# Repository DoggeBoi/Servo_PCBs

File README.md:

# Servo_PCBs
Collection of proof of consept and "production" PCBs 

Test PCB

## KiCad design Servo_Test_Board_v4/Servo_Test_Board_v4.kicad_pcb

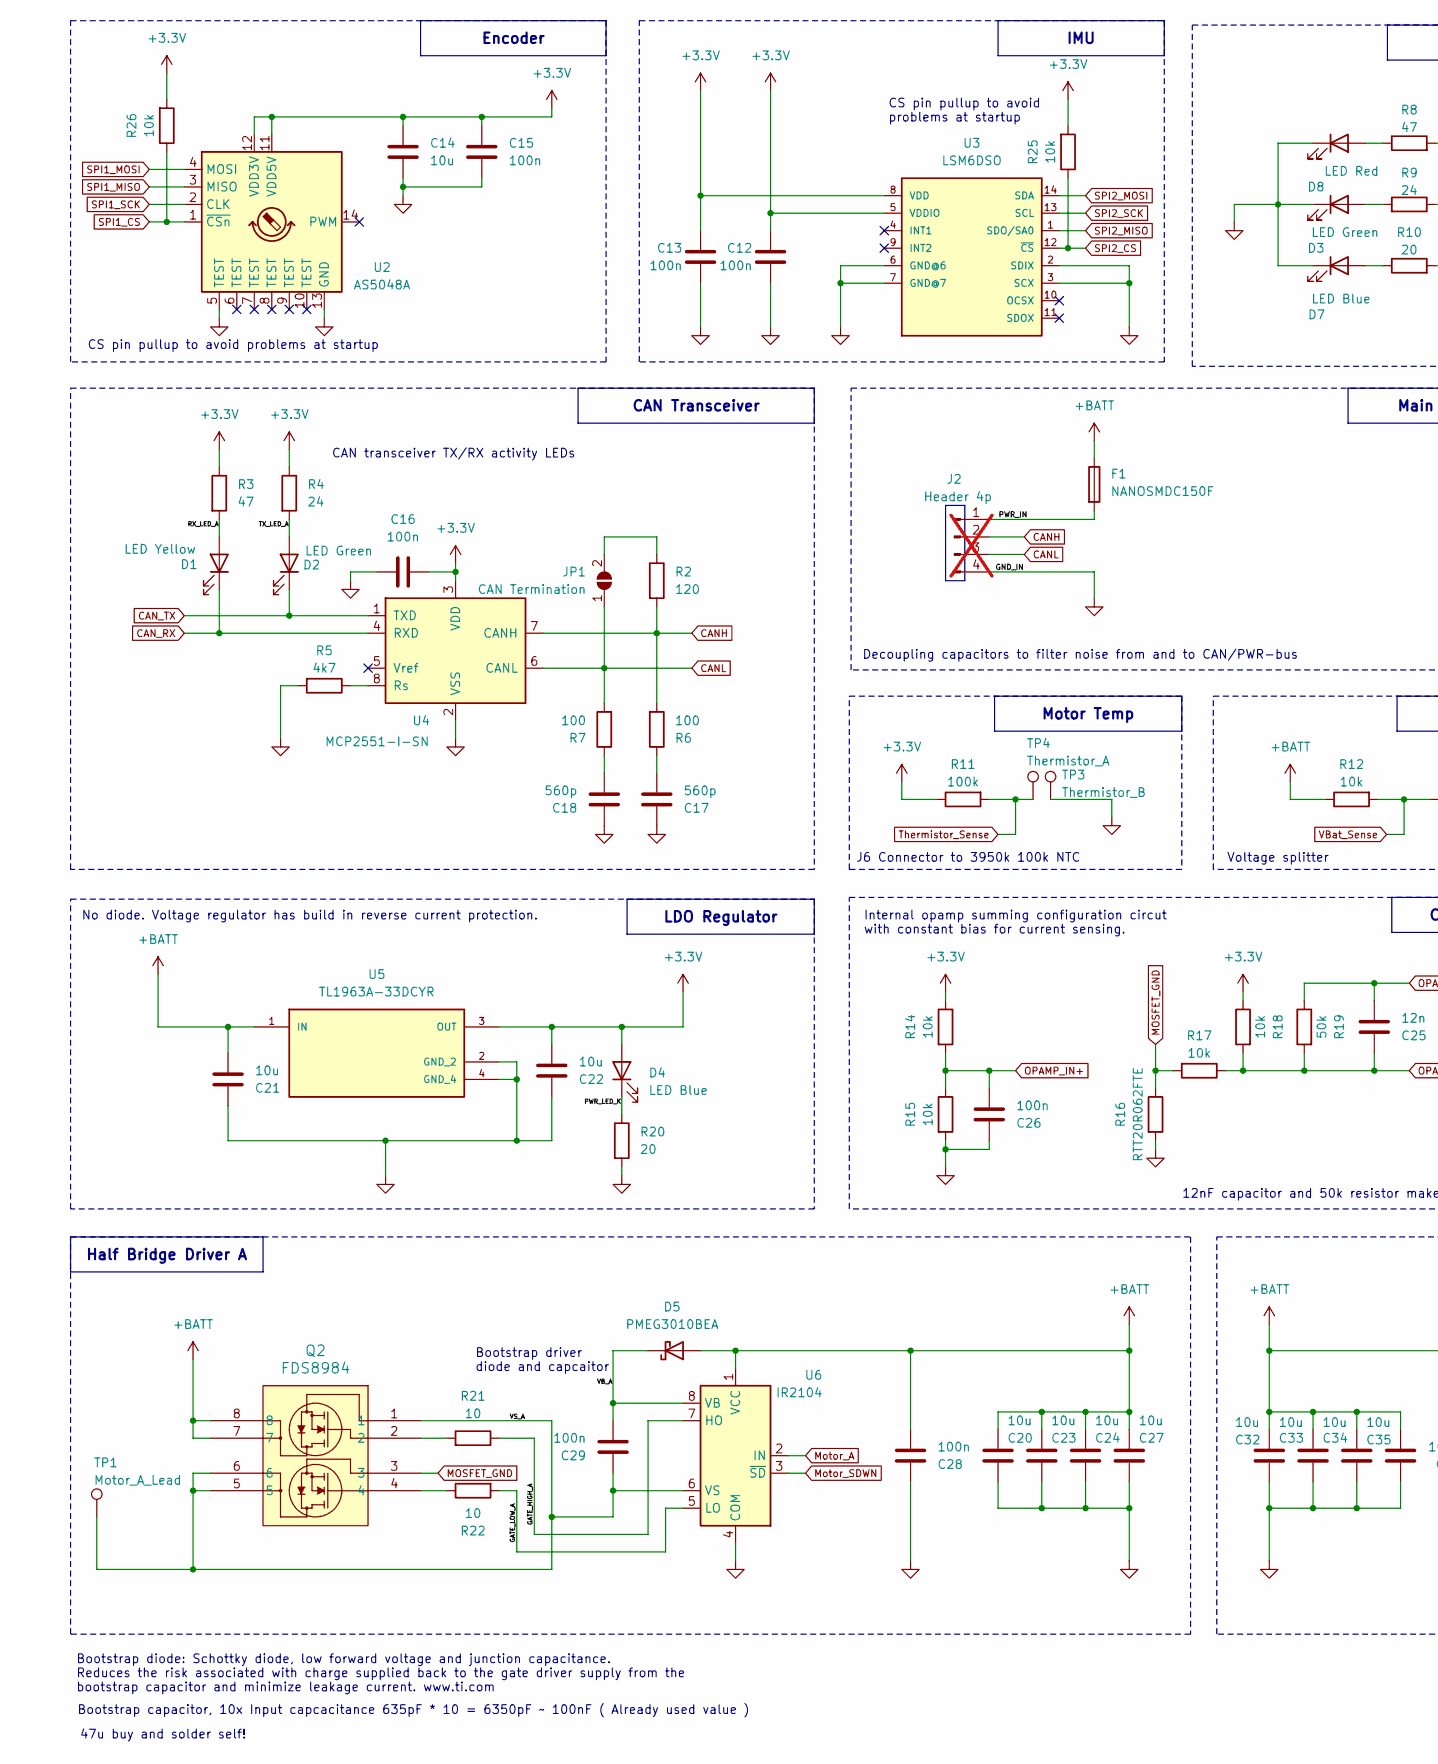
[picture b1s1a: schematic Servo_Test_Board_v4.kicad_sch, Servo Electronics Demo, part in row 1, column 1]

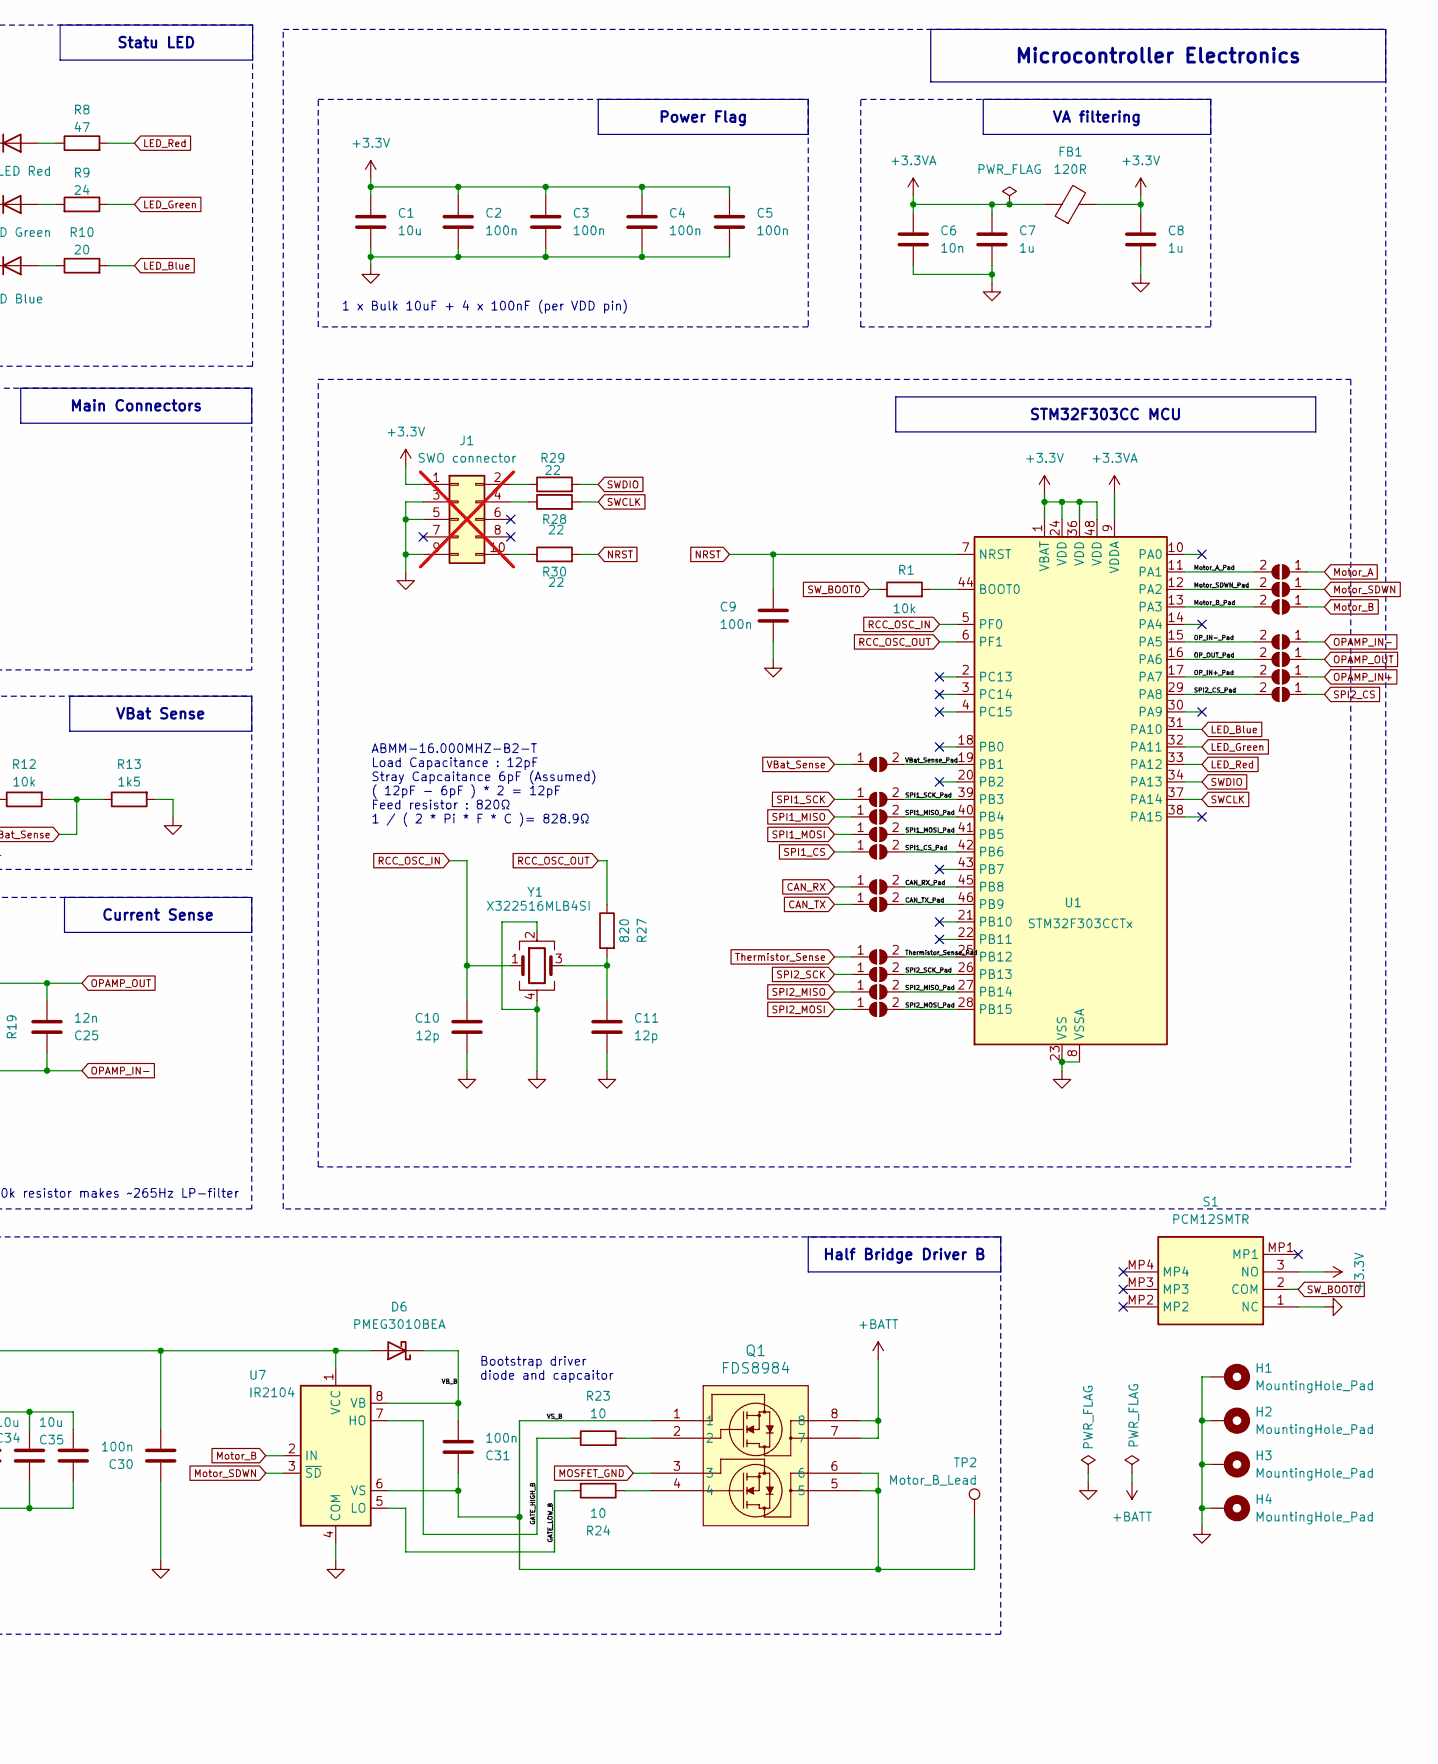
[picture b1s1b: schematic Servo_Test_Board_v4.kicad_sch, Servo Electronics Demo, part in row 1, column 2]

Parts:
C1, C14, C20, C21, C22, C23, C24, C27, C32, C33, C34, C35: 10u; C_0805_2012Metric
C2, C3, C4, C5, C9, C12, C13, C15, C16, C26, C28, C29, C30, C31: 100n; C_0402_1005Metric
C6: 10n; C_0402_1005Metric
C7, C8: 1u; C_0402_1005Metric
C10, C11: 12p; C_0402_1005Metric
C17, C18: 560p; C_0402_1005Metric
C25: 12n; C_0402_1005Metric
D1: LED Yellow; LED_0603_1608Metric
D2, D3: LED Green; LED_0603_1608Metric
D4, D7: LED Blue; LED_0603_1608Metric
D5, D6: PMEG3010BEA; D_SOD-323
D8: LED Red; LED_0603_1608Metric
F1: NANOSMDC150F; Fuse_1206_3216Metric
FB1: 120R; L_0603_1608Metric
H1, H2, H3, H4: MountingHole_Pad; MountingHole_3.2mm_M3_Pad_Via
J1: SWO connector; PinSocket_2x05_P2.54mm_Vertical; not fitted
J2: Header 4p; PinSocket_1x04_P2.54mm_Vertical; not fitted
JP1: CAN Termination; SolderJumper-2_P1.3mm_Open_RoundedPad1.0x1.5mm
JP2, JP3, JP4, JP5, JP6, JP7, JP8, JP9, JP10, JP11, JP12, JP14, JP15, JP16, JP17, JP18, JP19, JP20: SolderJumper_2_Open; SolderJumper-2_P1.3mm_Open_RoundedPad1.0x1.5mm
Q1, Q2: FDS8984; SOIC-8_3.9x4.9mm_P1.27mm
R1, R12, R14, R15, R17, R18, R25, R26: 10k; R_0402_1005Metric
R2: 120; R_0805_2012Metric
R3, R8: 47; R_0402_1005Metric
R4, R9: 24; R_0402_1005Metric
R5: 4k7; R_0402_1005Metric
R6, R7: 100; R_0402_1005Metric
R10, R20: 20; R_0402_1005Metric
R11: 100k; R_0402_1005Metric
R13: 1k5; R_0402_1005Metric
R16: RTT20R062FTE; R_2010_5025Metric_Pad1.40x2.65mm_HandSolder
R19: 50k; R_0402_1005Metric
R21, R22, R23, R24: 10; R_0402_1005Metric
R27: 820; R_0402_1005Metric
R28, R29, R30: 22; R_0402_1005Metric
S1: PCM12SMTR; Mouser Part Number 611-PCM12SMTR
TP1: Motor_A_Lead; TestPoint_Pad_2.5x2.5mm
TP2: Motor_B_Lead; TestPoint_Pad_2.5x2.5mm
TP3: Thermistor_B; TestPoint_Pad_2.0x2.0mm
TP4: Thermistor_A; TestPoint_Pad_2.0x2.0mm
U1: STM32F303CCTx; LQFP-48_7x7mm_P0.5mm
U2: AS5048A; TSSOP-14_4.4x5mm_P0.65mm
U3: LSM6DSO; LGA14L
U4: MCP2551-I-SN; SOIC-8_3.9x4.9mm_P1.27mm
U5: TL1963A-33DCYR; VREG_TL1963A-33DCYR; PARTREV G
U6, U7: IR2104; SOIC127P600X175-8N
Y1: X322516MLB4SI; Crystal_SMD_3225-4Pin_3.2x2.5mm

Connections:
+3.3V: C1.1, C2.1, C3.1, C4.1, C5.1, C8.1, C12.1, C13.1, C14.1, C15.1, C16.2, C22.1, D4.2 (A), FB1.2, J1.1, R3.1, R4.1, R11.1, R14.1, R18.1, R25.2, R26.2, S1.3 (NO), U1.1 (VBAT), U1.24 (VDD), U1.36 (VDD), U1.48 (VDD), U2.11 (VDD5V), U2.12 (VDD3V), U3.5 (VDDIO), U3.8 (VDD), U4.3 (VDD), U5.3 (OUT)
+3.3VA: C6.1, C7.1, FB1.1, U1.9 (VDDA)
+BATT: C20.1, C21.1, C23.1, C24.1, C27.1, C28.1, C30.1, C32.1, C33.1, C34.1, C35.1, D5.2 (A), D6.2 (A), F1.1, Q1.7, Q1.8, Q2.7, Q2.8, R12.1, U5.1 (IN), U6.1 (VCC), U7.1 (VCC)
/CAN_RX_Pad: JP7.2 (B), U1.45 (PB8)
/CAN_TX_Pad: JP8.2 (B), U1.46 (PB9)
/GATE_HIGH_A: R21.1, U6.7 (HO)
/GATE_HIGH_B: R23.1, U7.7 (HO)
/GATE_LOW_A: R22.2, U6.5 (LO)
/GATE_LOW_B: R24.2, U7.5 (LO)
/Motor_A_Pad: JP14.2 (B), U1.11 (PA1)
/Motor_B_Pad: JP16.2 (B), U1.13 (PA3)
/Motor_SDWN_Pad: JP15.2 (B), U1.12 (PA2)
/OP_IN+_Pad: JP19.2 (B), U1.17 (PA7)
/OP_IN-_Pad: JP17.2 (B), U1.15 (PA5)
/OP_OUT_Pad: JP18.2 (B), U1.16 (PA6)
/PWR_IN: F1.2, J2.1
/PWR_LED_K: D4.1 (K), R20.1
/RX_LED_A: D1.2 (A), R3.2
/SPI1_CS_Pad: JP6.2 (B), U1.42 (PB6)
/SPI1_MISO_Pad: JP4.2 (B), U1.40 (PB4)
/SPI1_MOSI_Pad: JP5.2 (B), U1.41 (PB5)
/SPI1_SCK_Pad: JP3.2 (B), U1.39 (PB3)
/SPI2_CS_Pad: JP20.2 (B), U1.29 (PA8)
/SPI2_MISO_Pad: JP11.2 (B), U1.27 (PB14)
/SPI2_MOSI_Pad: JP12.2 (B), U1.28 (PB15)
/SPI2_SCK_Pad: JP10.2 (B), U1.26 (PB13)
/TX_LED_A: D2.2 (A), R4.2
/Thermistor_Sense_Pad: JP9.2 (B), U1.25 (PB12)
/VB_A: C29.1, D5.1 (K), U6.8 (VB)
/VB_B: C31.1, D6.1 (K), U7.8 (VB)
/VBat_Sense_Pad: JP2.2 (B), U1.19 (PB1)
/VS_A: C29.2, Q2.1, Q2.5, Q2.6, TP1.1, U6.6 (VS)
/VS_B: C31.2, Q1.1, Q1.5, Q1.6, TP2.1, U7.6 (VS)
CANH: J2.2, R2.2, R6.2, U4.7 (CANH)
CANL: J2.3, JP1.1 (A), R7.2, U4.6 (CANL)
CAN_RX: D1.1 (K), JP7.1 (A), U4.4 (RXD)
CAN_TX: D2.1 (K), JP8.1 (A), U4.1 (TXD)
GND: C1.2, C2.2, C3.2, C4.2, C5.2, C6.2, C7.2, C8.2, C9.2, C10.2, C11.2, C12.2, C13.2, C14.2, C15.2, C16.1, C17.2, C18.2, C20.2, C21.2, C22.2, C23.2, C24.2, C26.2, C27.2, C28.2, C30.2, C32.2, C33.2, C34.2, C35.2, D3.1 (K), D7.1 (K), D8.1 (K), H1.1, H2.1, H3.1, H4.1, J1.3, J1.5, J1.9, J2.4, R5.2, R13.2, R15.2, R16.2, R20.2, S1.1 (NC), TP3.1, U1.8 (VSSA), U1.23 (VSS), U1.35 (VSS), U1.47 (VSS), U2.5 (TEST), U2.13 (GND), U3.2 (SDIX), U3.3 (SCX), U3.6 (GND@6), U3.7 (GND@7), U4.2 (VSS), U5.2 (GND_2), U5.4 (GND_4), U6.4 (COM), U7.4 (COM), Y1.2, Y1.4
LED_Blue: R10.2, U1.31 (PA10)
LED_Green: R9.1, U1.32 (PA11)
LED_Red: R8.2, U1.33 (PA12)
MOSFET_GND: Q1.3, Q2.3, R16.1, R17.2
Motor_A: JP14.1 (A), U6.2 (IN)
Motor_B: JP16.1 (A), U7.2 (IN)
Motor_SDWN: JP15.1 (A), U6.3 (~SD), U7.3 (~SD)
NRST: C9.1, R30.2, U1.7 (NRST)
unnamed: C11.1, R27.2, Y1.3
unnamed: C17.1, R6.1
unnamed: C18.1, R7.1
unnamed: D3.2 (A), R9.2
unnamed: D7.2 (A), R10.1
unnamed: D8.2 (A), R8.1
unnamed: J1.2, R29.1
unnamed: J1.4, R28.1
unnamed: J1.10, R30.1
unnamed: JP1.2 (B), R2.1
unnamed: Q1.2, R23.2
unnamed: Q1.4, R24.1
unnamed: Q2.2, R21.2
unnamed: Q2.4, R22.1
unnamed: R1.2, U1.44 (BOOT0)
unnamed: R5.1, U4.8 (Rs)
OPAMP_IN+: C26.1, JP19.1 (A), R14.2, R15.1
OPAMP_IN-: C25.2, JP17.1 (A), R17.1, R18.2, R19.2
OPAMP_OUT: C25.1, JP18.1 (A), R19.1
RCC_OSC_IN: C10.1, U1.5 (PF0), Y1.1
RCC_OSC_OUT: R27.1, U1.6 (PF1)
SPI1_CS: JP6.1 (A), R26.1, U2.1 (~CSn)
SPI1_MISO: JP4.1 (A), U2.3 (MISO)
SPI1_MOSI: JP5.1 (A), U2.4 (MOSI)
SPI1_SCK: JP3.1 (A), U2.2 (CLK)
SPI2_CS: JP20.1 (A), R25.1, U3.12 (~CS)
SPI2_MISO: JP11.1 (A), U3.1 (SDO/SA0)
SPI2_MOSI: JP12.1 (A), U3.14 (SDA)
SPI2_SCK: JP10.1 (A), U3.13 (SCL)
SWCLK: R28.2, U1.37 (PA14)
SWDIO: R29.2, U1.34 (PA13)
SW_BOOT0: R1.1, S1.2 (COM)
Thermistor_Sense: JP9.1 (A), R11.2, TP4.1
VBat_Sense: JP2.1 (A), R12.2, R13.1

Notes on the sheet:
Main Connectors
Power Flag
Half Bridge Driver B
STM32F303CC MCU
Current Sense
Statu LED
IMU
LDO Regulator
Microcontroller Electronics
VBat Sense
Motor Temp
Encoder
CAN Transceiver
VA filtering
Half Bridge Driver A
Bootstrap capacitor, 10x Input capcacitance 635pF * 10 = 6350pF ~ 100nF ( Already used value )
Bootstrap diode: Schottky diode, low forward voltage and junction capacitance. Reduces the risk associated with charge supplied back to the gate driver supply from the bootstrap capacitor and minimize leakage current. www.ti.com
No diode. Voltage regulator has build in reverse current protection.
Decoupling capacitors to filter noise from and to CAN/PWR-bus
Bootstrap driver diode and capcaitor
ABMM-16.000MHZ-B2-T Load Capacitance : 12pF Stray Capcaitance 6pF (Assumed) ( 12pF - 6pF ) * 2 = 12pF Feed resistor : 820Ω 1 / ( 2 * Pi * F * C )= 828.9Ω
12nF capacitor and 50k resistor makes ~265Hz LP-filter
CS pin pullup to avoid problems at startup
CS pin pullup to avoid problems at startup
Internal opamp summing configuration circut with constant bias for current sensing.
Voltage splitter
CAN transceiver TX/RX activity LEDs
47u buy and solder self!
1 x Bulk 10uF + 4 x 100nF (per VDD pin)
J6 Connector to 3950k 100k NTC

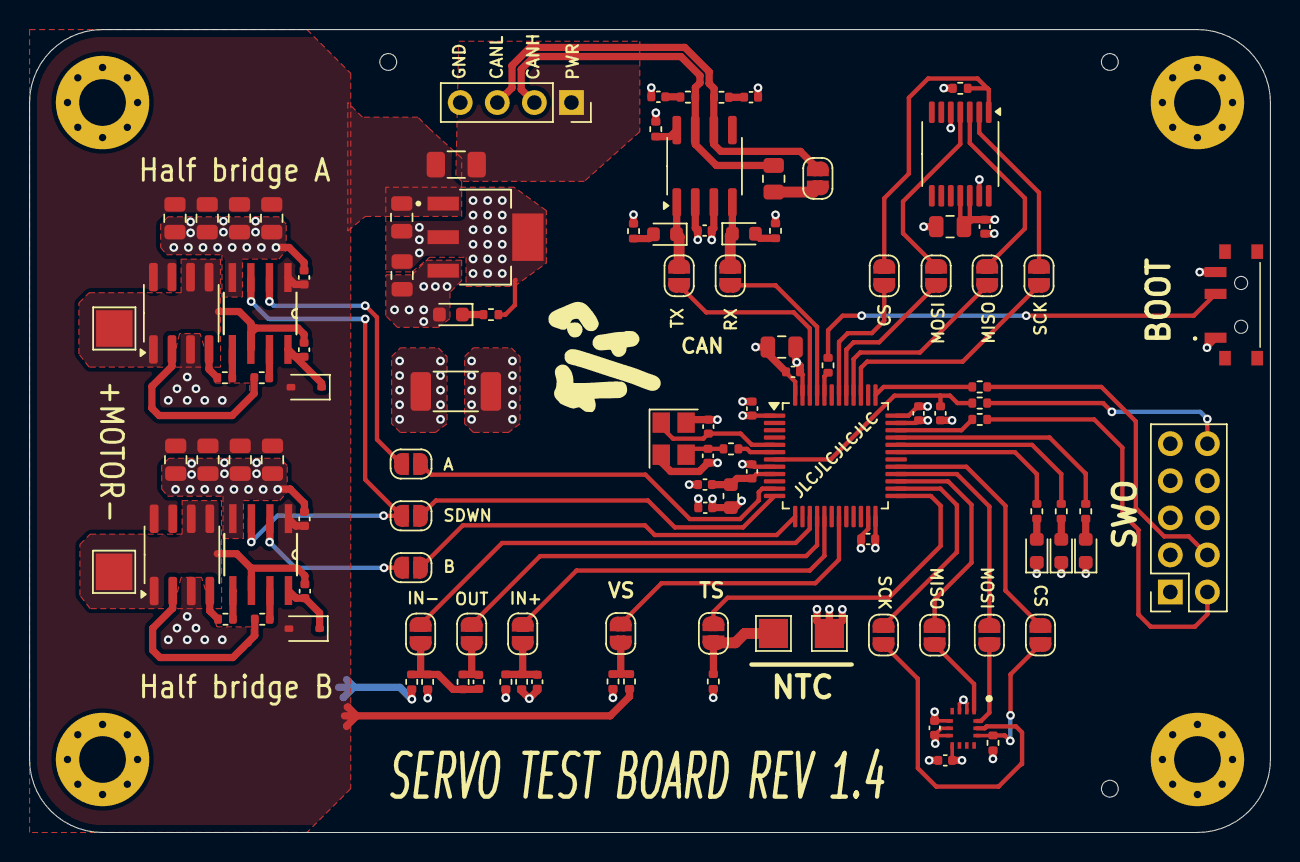
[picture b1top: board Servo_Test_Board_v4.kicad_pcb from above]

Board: 4 copper layers, 85.0 x 55.0 mm, 114 parts (0 on the bottom side), 80 nets.

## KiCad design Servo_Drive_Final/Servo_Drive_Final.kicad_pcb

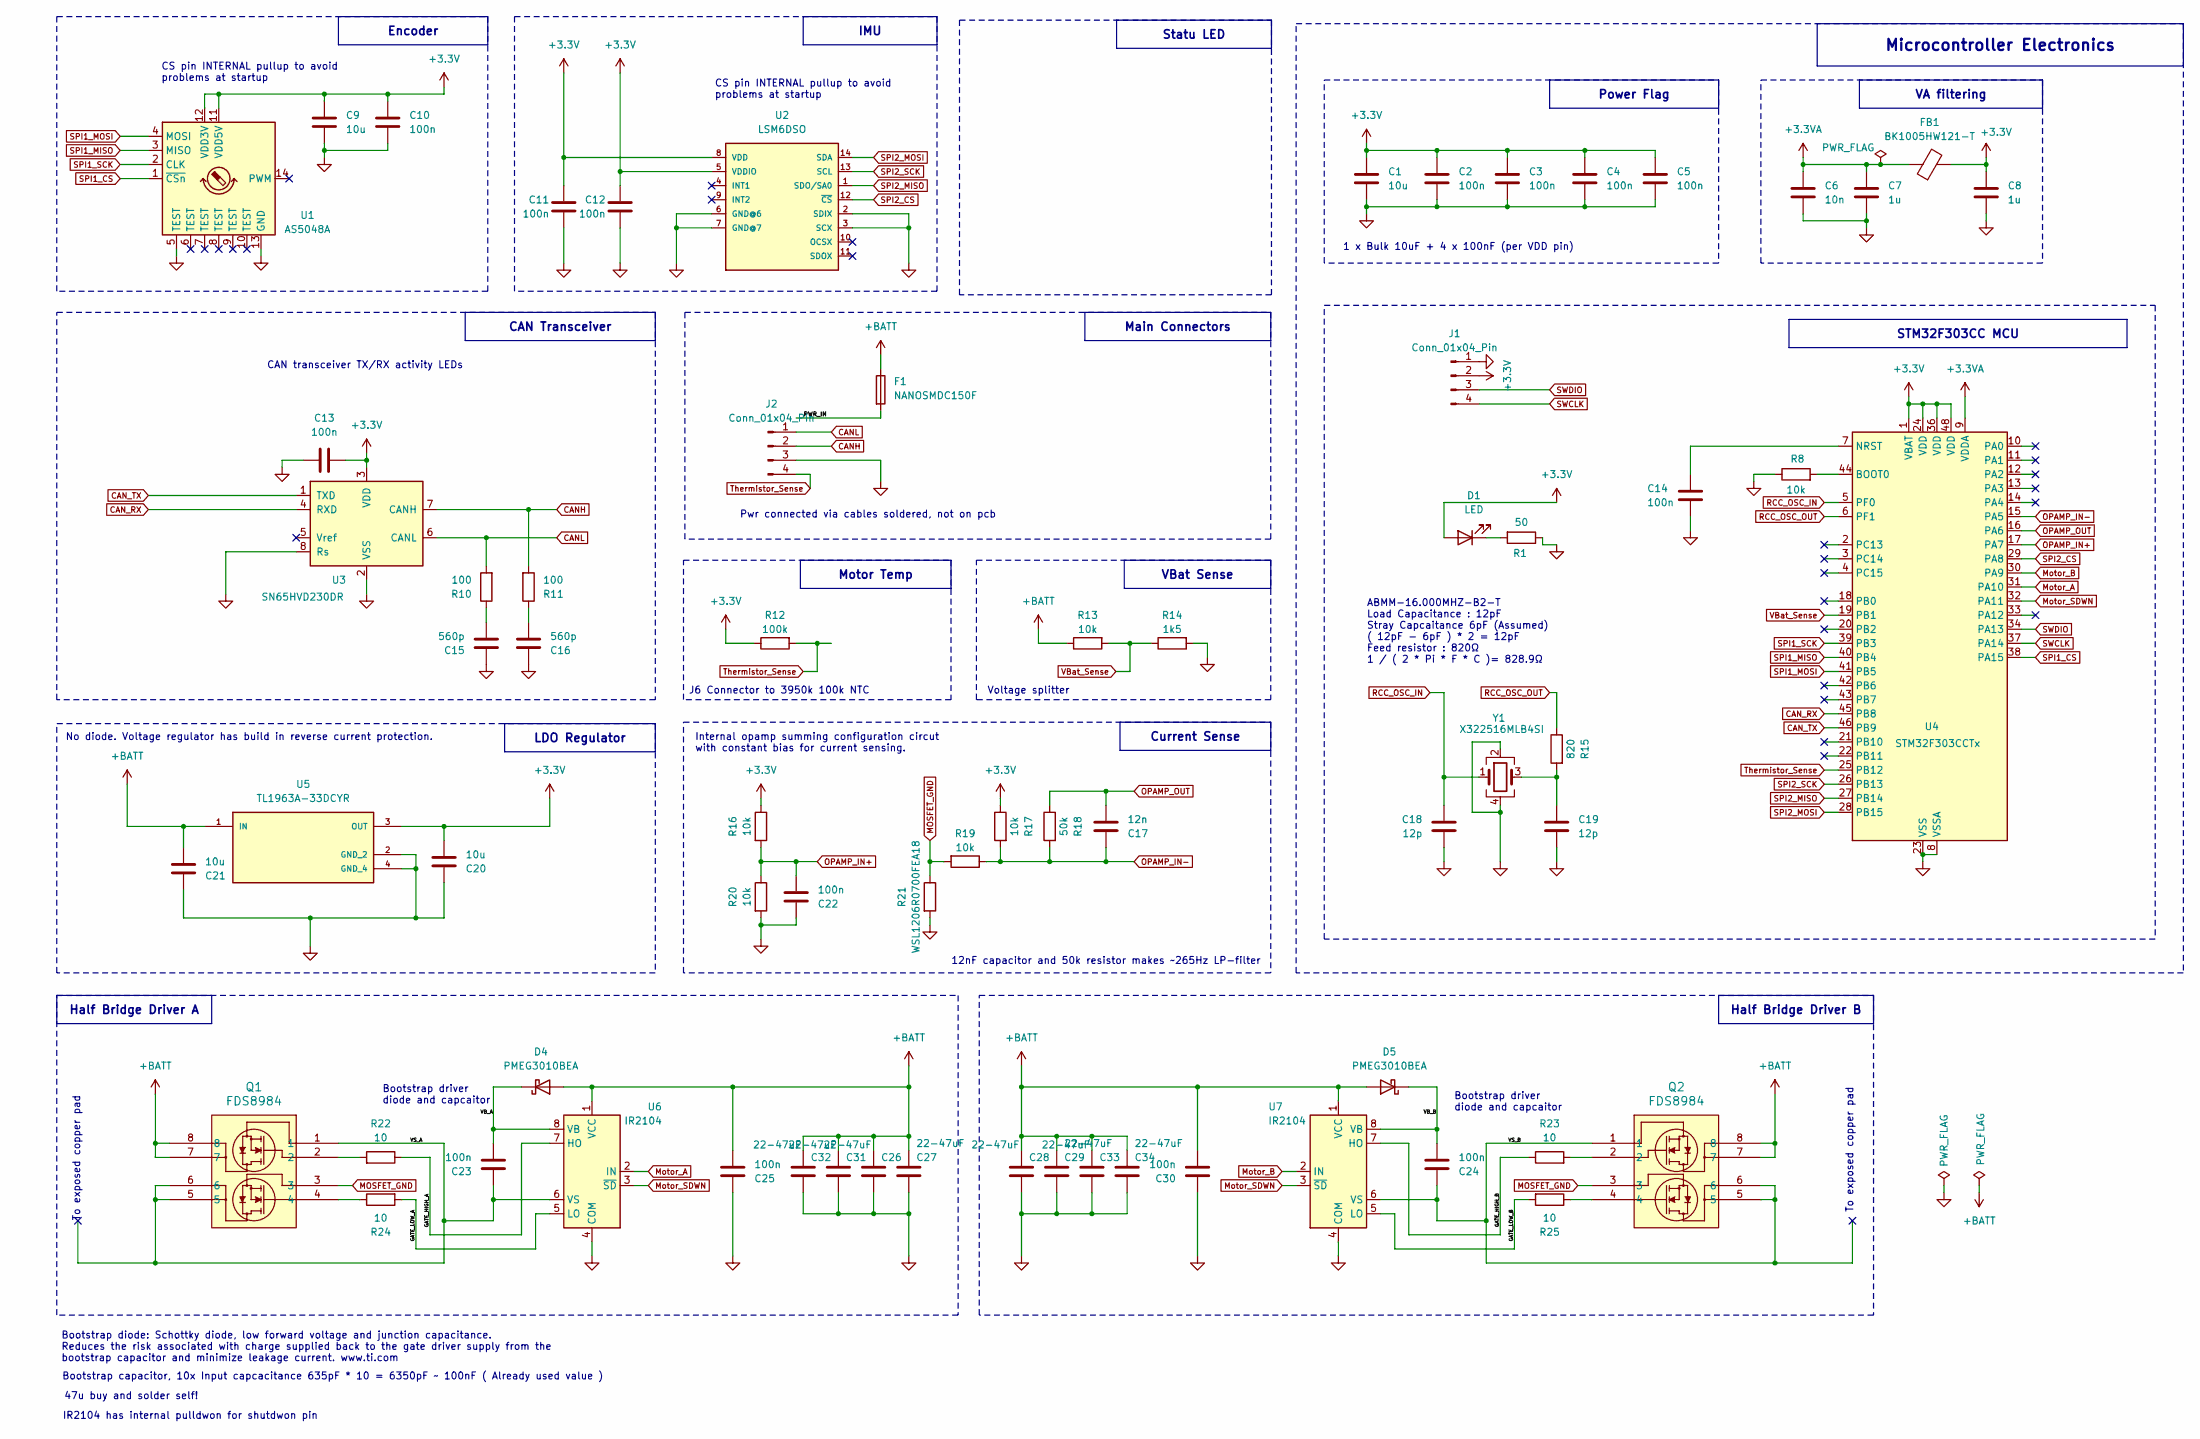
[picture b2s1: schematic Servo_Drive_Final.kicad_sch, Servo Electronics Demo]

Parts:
C1, C9, C20, C21: 10u; C_0805_2012Metric
C2, C3, C4, C5, C10, C11, C12, C13, C14, C22, C23, C24, C25, C30: 100n; C_0402_1005Metric
C6: 10n; C_0402_1005Metric
C7, C8: 1u; C_0402_1005Metric
C15, C16: 560p; C_0402_1005Metric
C17: 12n; C_0402_1005Metric
C18, C19: 12p; C_0402_1005Metric
C26, C27, C28, C29, C31, C32, C33, C34: 22-47uF; C_1206_3216Metric
D1: LED; LED_0603_1608Metric
D4, D5: PMEG3010BEA; D_SOD-323
F1: NANOSMDC150F; Fuse_1206_3216Metric
FB1: BK1005HW121-T; L_0402_1005Metric
J1, J2: Conn_01x04_Pin; CUSTOM_PAD
Q1, Q2: FDS8984; Custom SOIC-8
R1: 50; R_0402_1005Metric
R8, R13, R16, R17, R19, R20: 10k; R_0402_1005Metric
R10, R11: 100; R_0402_1005Metric
R12: 100k; R_0402_1005Metric
R14: 1k5; R_0402_1005Metric
R15: 820; R_0402_1005Metric
R18: 50k; R_0402_1005Metric
R21: WSL1206R0700FEA18; R_1206_3216Metric
R22, R23, R24, R25: 10; R_0402_1005Metric
U1: AS5048A; TSSOP-14_4.4x5mm_P0.65mm
U2: LSM6DSO; Bosch_LGA-14_3x2.5mm_P0.5mm
U3: SN65HVD230DR; SOIC-8_3.9x4.9mm_P1.27mm
U4: STM32F303CCTx; LQFP-48_7x7mm_P0.5mm
U5: TL1963A-33DCYR; VREG_TL1963A-33DCYR-SERVO_CUSTOM; PARTREV G
U6, U7: IR2104; Custom SOIC-8
Y1: X322516MLB4SI; Crystal_SMD_3225-4Pin_3.2x2.5mm

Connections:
+3.3V: C1.1, C2.1, C3.1, C4.1, C5.1, C8.1, C9.1, C10.1, C11.1, C12.1, C13.2, C20.1, D1.2 (A), FB1.2, J1.2, R12.1, R16.1, R17.1, U1.11 (VDD5V), U1.12 (VDD3V), U2.5 (VDDIO), U2.8 (VDD), U3.3 (VDD), U4.1 (VBAT), U4.24 (VDD), U4.36 (VDD), U4.48 (VDD), U5.3 (OUT)
+3.3VA: C6.1, C7.1, FB1.1, U4.9 (VDDA)
+BATT: C21.1, C25.1, C26.1, C27.1, C28.1, C29.1, C30.1, C31.1, C32.1, C33.1, C34.1, D4.2 (A), D5.2 (A), F1.1, Q1.7, Q1.8, Q2.7, Q2.8, R13.1, U5.1 (IN), U6.1 (VCC), U7.1 (VCC)
/GATE_HIGH_A: R22.1, U6.7 (HO)
/GATE_HIGH_B: R23.1, U7.7 (HO)
/GATE_LOW_A: R24.2, U6.5 (LO)
/GATE_LOW_B: R25.2, U7.5 (LO)
/PWR_IN: F1.2
/VB_A: C23.1, D4.1 (K), U6.8 (VB)
/VB_B: C24.1, D5.1 (K), U7.8 (VB)
/VS_A: C23.2, Q1.1, Q1.5, Q1.6, U6.6 (VS)
/VS_B: C24.2, Q2.1, Q2.5, Q2.6, U7.6 (VS)
CANH: J2.2, R11.2, U3.7 (CANH)
CANL: J2.1, R10.2, U3.6 (CANL)
CAN_RX: U3.4 (RXD), U4.45 (PB8)
CAN_TX: U3.1 (TXD), U4.46 (PB9)
GND: C1.2, C2.2, C3.2, C4.2, C5.2, C6.2, C7.2, C8.2, C9.2, C10.2, C11.2, C12.2, C13.1, C14.2, C15.2, C16.2, C18.2, C19.2, C20.2, C21.2, C22.2, C25.2, C26.2, C27.2, C28.2, C29.2, C30.2, C31.2, C32.2, C33.2, C34.2, J1.1, J2.3, R1.1, R8.1, R14.2, R20.2, R21.2, U1.5 (TEST), U1.13 (GND), U2.2 (SDIX), U2.3 (SCX), U2.6 (GND@6), U2.7 (GND@7), U3.2 (VSS), U3.8 (Rs), U4.8 (VSSA), U4.23 (VSS), U4.35 (VSS), U4.47 (VSS), U5.2 (GND_2), U5.4 (GND_4), U6.4 (COM), U7.4 (COM), Y1.2, Y1.4
MOSFET_GND: Q1.3, Q2.3, R19.2, R21.1
Motor_A: U4.31 (PA10), U6.2 (IN)
Motor_B: U4.30 (PA9), U7.2 (IN)
Motor_SDWN: U4.32 (PA11), U6.3 (~SD), U7.3 (~SD)
unnamed: C15.1, R10.1
unnamed: C16.1, R11.1
unnamed: C19.1, R15.2, Y1.3
unnamed: D1.1 (K), R1.2
unnamed: Q1.2, R22.2
unnamed: Q1.4, R24.1
unnamed: Q2.2, R23.2
unnamed: Q2.4, R25.1
unnamed: R8.2, U4.44 (BOOT0)
unnamed: C14.1, U4.7 (NRST)
OPAMP_IN+: C22.1, R16.2, R20.1, U4.17 (PA7)
OPAMP_IN-: C17.2, R17.2, R18.2, R19.1, U4.15 (PA5)
OPAMP_OUT: C17.1, R18.1, U4.16 (PA6)
RCC_OSC_IN: C18.1, U4.5 (PF0), Y1.1
RCC_OSC_OUT: R15.1, U4.6 (PF1)
SPI1_CS: U1.1 (~CSn), U4.38 (PA15)
SPI1_MISO: U1.3 (MISO), U4.40 (PB4)
SPI1_MOSI: U1.4 (MOSI), U4.41 (PB5)
SPI1_SCK: U1.2 (CLK), U4.39 (PB3)
SPI2_CS: U2.12 (~CS), U4.29 (PA8)
SPI2_MISO: U2.1 (SDO/SA0), U4.27 (PB14)
SPI2_MOSI: U2.14 (SDA), U4.28 (PB15)
SPI2_SCK: U2.13 (SCL), U4.26 (PB13)
SWCLK: J1.4, U4.37 (PA14)
SWDIO: J1.3, U4.34 (PA13)
Thermistor_Sense: J2.4, R12.2, U4.25 (PB12)
VBat_Sense: R13.2, R14.1, U4.19 (PB1)

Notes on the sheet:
Main Connectors
Power Flag
Half Bridge Driver B
STM32F303CC MCU
Current Sense
Statu LED
IMU
LDO Regulator
Microcontroller Electronics
VBat Sense
Motor Temp
Encoder
CAN Transceiver
VA filtering
Half Bridge Driver A
Bootstrap capacitor, 10x Input capcacitance 635pF * 10 = 6350pF ~ 100nF ( Already used value )
Bootstrap diode: Schottky diode, low forward voltage and junction capacitance. Reduces the risk associated with charge supplied back to the gate driver supply from the bootstrap capacitor and minimize leakage current. www.ti.com
No diode. Voltage regulator has build in reverse current protection.
To exposed copper pad
Bootstrap driver diode and capcaitor
ABMM-16.000MHZ-B2-T Load Capacitance : 12pF Stray Capcaitance 6pF (Assumed) ( 12pF - 6pF ) * 2 = 12pF Feed resistor : 820Ω 1 / ( 2 * Pi * F * C )= 828.9Ω
12nF capacitor and 50k resistor makes ~265Hz LP-filter
CS pin INTERNAL pullup to avoid problems at startup
Internal opamp summing configuration circut with constant bias for current sensing.
Voltage splitter
CAN transceiver TX/RX activity LEDs
IR2104 has internal pulldwon for shutdwon pin
47u buy and solder self!
Pwr connected via cables soldered, not on pcb
1 x Bulk 10uF + 4 x 100nF (per VDD pin)
J6 Connector to 3950k 100k NTC

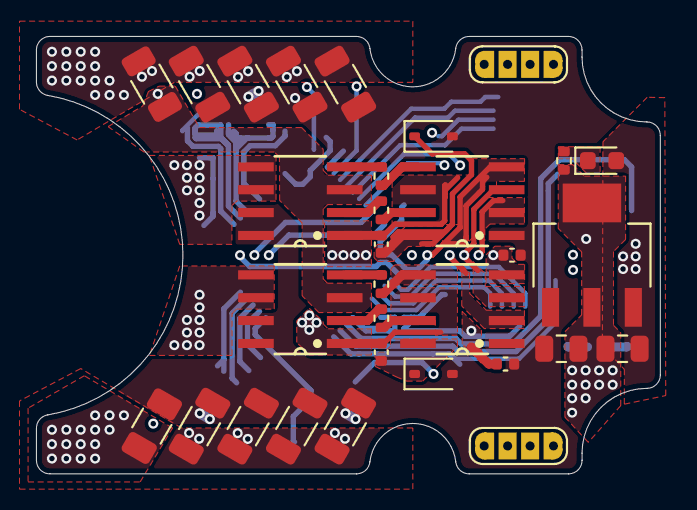
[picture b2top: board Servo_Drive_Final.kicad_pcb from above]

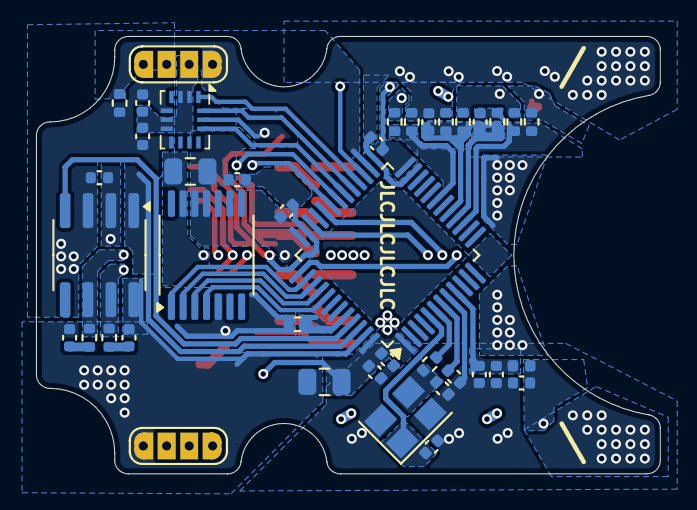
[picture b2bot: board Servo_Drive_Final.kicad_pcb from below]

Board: 4 copper layers, 34.7 x 24.3 mm, 69 parts (38 on the bottom side), 47 nets.
